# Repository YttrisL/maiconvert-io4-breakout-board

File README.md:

# maiconvert-io4-breakout-board

This breakout board is designed to be a helper for maimai FiNALE cabinet conversion to DX, to help people configure an IO4 home setup with a custom controller, or to serve as a testing setup for an IO4.

It can easily be installed between an IO4 and the cabinet harness thanks to its passthrough connector, supporting both FiNALE and genuine DX CN3 harnesses. If you do not have a harness to use, the board fans every I/O out to labeled JST-XH connectors and adds on-board test switches and RGB indicator LEDs.

<p align="center">

</p>
<p align="center"><sub>Schematic - PCB 3D render (front) - PCB 3D render (back) - click any image for the full-size version</sub></p>

<p align="center">

</p>
<p align="center"><sub>Fabricated and assembled board, wired to an IO4 and a generic PSU - top view - IO4 side - breakout board side</sub></p>

## Installation

The board requires 3 connections :

* You need to plug the CN3 and CN9 connectors from the IO4. The actual connector on IO4 is a JST-RA 2x30 pins, but you can use any connector with a pitch of 2.54mm. An IDC ribbon cable with two female connectors works great for that, you'll need a 2x30 and a 2x10.
* You also need to provide a clean 12V to the terminal block. If you're using the board in a cab, use the 12V PSU dedicated to LED lighting. Do not steal the 12V from the IO4.

There is basic protection at the entrance on the 12V rail on the board to prevent reverse polarity, but you are still responsible for providing clean current. The input is sized for 15A, though it should absolutely never reach that amount of current. There is a fuse right next to the connector. In case of issue, check that first.

## Use-cases

The board is intended for three parallel use-cases, designed with as little complexity and onboard logic as possible to ensure a minimal-to-null impact on gameplay. As such, you can use this board as a permanent addition to any cab without trade-off.

### Helper for maimai FiNALE cabinet conversion to DX

The main use-case. Install this board next to your IO4 in your FiNALE cab, connect CN3 and CN9 from the IO4, and plug in the cabinet's harness on the J3 connector.

There is a minor difference between the DX and FiNALE harness. On FiNALE's, the "Coin Locker" pin is at the position 51. On DX's, it is at the position 53, and 51 has been assigned to a billboard LED signal instead. To handle this difference, there are three pins right under the passthrough connector.

- **If your harness is a genuine DX (or an already modified FiNALE one)** :
  - Place a jumper over the two pins on the right
- **If your harness is an unmodified FiNALE** :
  - Place a jumper over the two pins on the left

The connection to the gameplay buttons is handled by the harness. However, since these do not exist on a FiNALE cab you will need to expose and connect the 1P and 2P SELECT BUTTONS to the appropriate JST-XH connectors.

The LED signals that DX now sends through the IO4 are exposed on the upper part of the board. You need to provide your own 12V power source for these to work. I advise using the cab's 12V LED PSU for this. Once properly powered, the test LEDs will light up with the signal sent by the game. You can now plug in your actual LEDs in the appropriate connectors. J23 and J24 for the billboard LED are designed to be compatible with the existing cables in a FiNALE cab covering the upper LEDs and the woofer LEDs. You will likely need a cable extension but you can plug those in directly on the board.

When the board has a CN3 harness plugged in on the passthrough J3 connector, only the `Test`, `Coin`, `Service`, and `1-2P Select` onboard tactile switches will work. The gameplay buttons' onboard tactile switches are disabled in this configuration.

Thanks to this, the board can be installed in the cab as a permanent addition with zero impact on performance.

### IO4 breakout board for home setup

If for your own reasons you want to run an actual IO4 in your home setup with your personal custom game controller, you can use this board to fan out the connectors from the IO4. Just connect the CN3 from the IO4 and plug in your buttons on the appropriate JST-XH connectors.

*Note :* the game expects buttons to be present. If you try running the board without plugging in the buttons, you will notice that the gameplay inputs are considered as continuously "pressed". See the "Test setup" case for ways to go around that, but it is not advised to use this board's tactile switches alone for actual gameplay.

If you want to install your own LEDs driven by the IO4, you can also do that. You need to plug in the CN9 connector with an IDC 2x10 female-female cable. You will also need to supply the 12V line with your own Mean Well PSU. Test LEDs should now light up as the game drives them and you can use the connectors to plug in your own LED strips. **Warning**: Do not put too much stress on the board, the copper is sized appropriately (excessively even) for the amount of current an actual cabinet's LED would draw, but if you put more load on the board then results may be unpredictable.

**Important note :** The game will not detect the IO4 if EXV is not bridged with 5V. In a normal cabinet, this is done by the harness. Here, **you need to install a jumper on the two dedicated floating pins situated next to the top right of the passthrough connector** normally dedicated to the harness.

In this configuration, both tactile buttons and gameplay buttons will work at the same time.

### A testing setup for an IO4

You may want to use the board to quickly test an IO4 you just received or you suspect faulty. Plug the CN3 and CN9 from the IO4, and plug your own 12V supply.

The LED section should light up as soon as the game starts driving them, you can use the onboard tactile switches to trigger the signals. Using it as-is though, you'll notice that the gameplay buttons' tactile switches do not actually work.

Because of the way the IO4 handles the gameplay buttons, it is normally not possible to test those signals if the actual button is not properly connected. This is because the IO4 natively puts that signal at HIGH, and the button assembly itself pulls it to LOW once it's connected. The IO considers that HIGH is "pressed", and LOW is "not pressed". Because of that behavior, unconnected buttons remain at HIGH and are always considered pressed.

To go around that, **for testing purposes you can put a jumper between pin 2 and 3 of the JST-XH connector**. That will bridge the signal in a forced LOW state that you can then activate using the onboard tactile button.

### Other uses

You might find other uses for this board that I hadn't thought about, though be aware that anything beyond the previous scope is not intended and the board behavior is not guaranteed.

## Fabrication

The PCB is designed to be fabricated bare at JLCPCB. See gerbers in `production/`.  
Components have to be hand-soldered. See the BOM in the `bom/` folder.

You can technically make JLCPCB assemble the board for you, but there are a lot of THT connectors on the board, and JLCPCB charges extra for each one of them. The extra price is most likely not worth the time, but you decide.

### To fab the PCB

On [jlcpcb.com](https://jlcpcb.com/) :

- Click "*Add gerber file*" and upload `production/maiconv-io4-breakout-board-gerbers.zip` as-is.
  - The auto-detected options already match this board (2 layers, 1.6 mm, 1 oz copper), just choose a solder mask color.
- Leave *PCB Assembly* off (all THT).
- Check the Gerber preview.
- Order.

### To order the parts

On [digikey.com](https://www.digikey.com/) :

- Go to *myLists* → *Create a New List* → *Upload a File* and upload `bom/digikey_upload.csv`.
- Map the columns to *Quantity* / *DigiKey Part Number* / *Customer Reference* (the header already uses those names).
- Review any out-of-stock lines, then add the list to your cart.
- Order.

## License

This board is distributed under the `CERN Open Hardware Licence Version 2 - Strongly Reciprocal` license. You are encouraged to share this page as much as you like and improve on the original design.

Please note that while the license doesn't strictly forbid it, I ask you to be a decent human being and to not make a business out of selling this board to anyone. This is free and should remain so. That being said, feel free to resell extra copies you may have gotten with your fabrication (they usually make them by stack of 5) to other people, as long as you do not charge an extortionate extra for them.

## Disclaimer

While I took great caution to make sure every component was properly sized, I am not a certified electronics engineer. This board is distributed freely without any guarantees, and you use it at your own risk. That being said, every component has been selected way above the actual minimal requirement of the circuit, so there shouldn't be any major issue.

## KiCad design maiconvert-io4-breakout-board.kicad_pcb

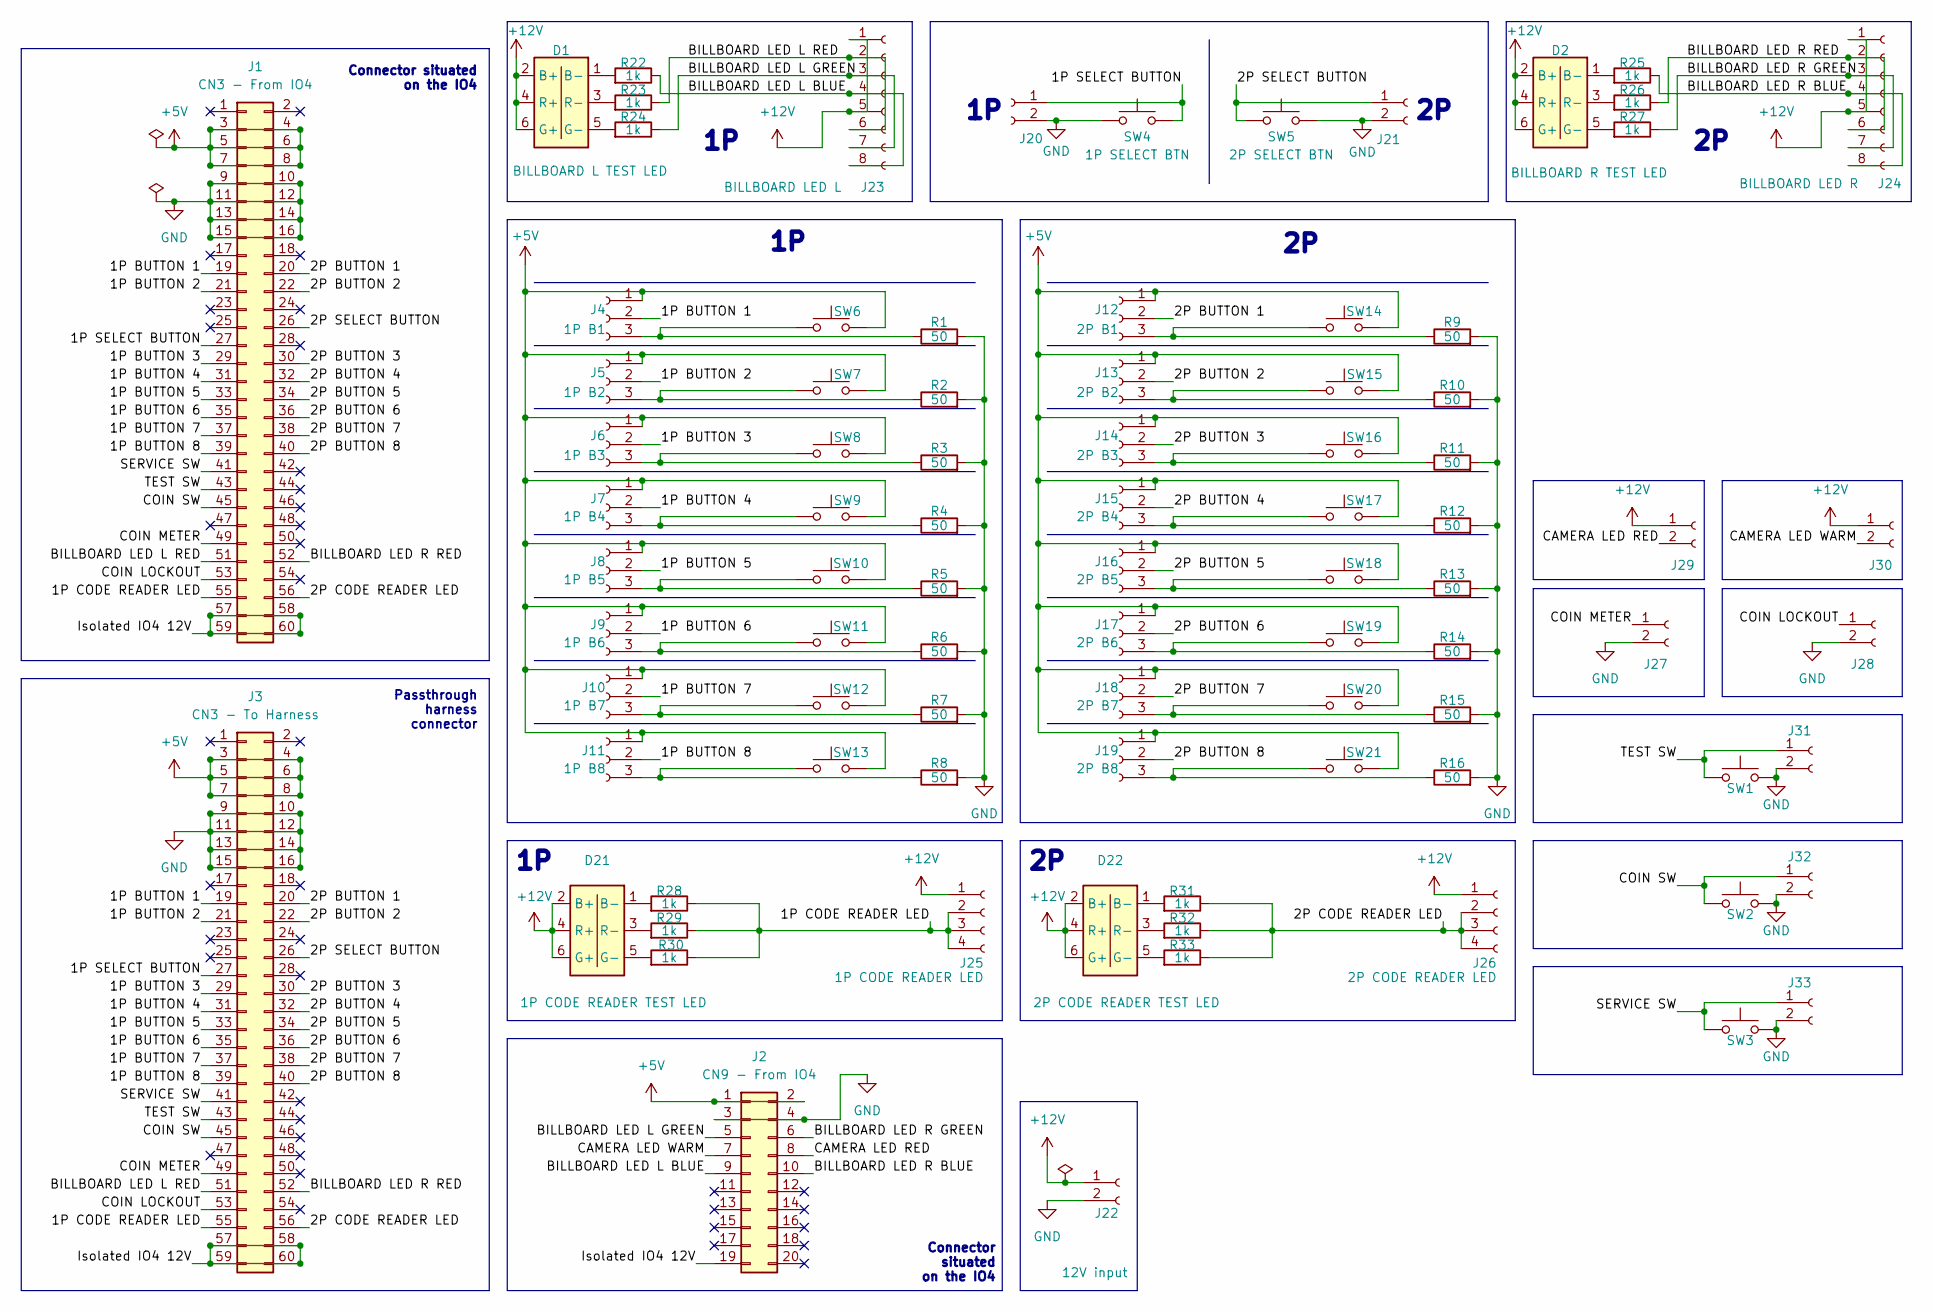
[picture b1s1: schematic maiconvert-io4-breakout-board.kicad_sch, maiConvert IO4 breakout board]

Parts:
D1: BILLBOARD L TEST LED; LED_RGB_Wurth_WL-SFTW_150352M173300; Digi-Key 732-11999-1-ND
D2: BILLBOARD R TEST LED; LED_RGB_Wurth_WL-SFTW_150352M173300; Digi-Key 732-11999-1-ND
D21: 1P CODE READER TEST LED; LED_RGB_Wurth_WL-SFTW_150352M173300; Digi-Key 732-11999-1-ND
D22: 2P CODE READER TEST LED; LED_RGB_Wurth_WL-SFTW_150352M173300; Digi-Key 732-11999-1-ND
J1: CN3 - From IO4; IDC-Header_2x30_P2.54mm_Vertical; Digi-Key 2057-BHR-60-VUA-ND
J2: CN9 - From IO4; IDC-Header_2x10_P2.54mm_Vertical; Digi-Key 2057-BHR-20-VUA-ND
J3: CN3 - To Harness; IDC-Header_2x30_P2.54mm_Vertical; Digi-Key 2057-BHR-60-VUA-ND
J4: 1P B1; JST_XH_B3B-XH-A_1x03_P2.50mm_Vertical; Digi-Key 455-2248-ND
J5: 1P B2; JST_XH_B3B-XH-A_1x03_P2.50mm_Vertical; Digi-Key 455-2248-ND
J6: 1P B3; JST_XH_B3B-XH-A_1x03_P2.50mm_Vertical; Digi-Key 455-2248-ND
J7: 1P B4; JST_XH_B3B-XH-A_1x03_P2.50mm_Vertical; Digi-Key 455-2248-ND
J8: 1P B5; JST_XH_B3B-XH-A_1x03_P2.50mm_Vertical; Digi-Key 455-2248-ND
J9: 1P B6; JST_XH_B3B-XH-A_1x03_P2.50mm_Vertical; Digi-Key 455-2248-ND
J10: 1P B7; JST_XH_B3B-XH-A_1x03_P2.50mm_Vertical; Digi-Key 455-2248-ND
J11: 1P B8; JST_XH_B3B-XH-A_1x03_P2.50mm_Vertical; Digi-Key 455-2248-ND
J12: 2P B1; JST_XH_B3B-XH-A_1x03_P2.50mm_Vertical; Digi-Key 455-2248-ND
J13: 2P B2; JST_XH_B3B-XH-A_1x03_P2.50mm_Vertical; Digi-Key 455-2248-ND
J14: 2P B3; JST_XH_B3B-XH-A_1x03_P2.50mm_Vertical; Digi-Key 455-2248-ND
J15: 2P B4; JST_XH_B3B-XH-A_1x03_P2.50mm_Vertical; Digi-Key 455-2248-ND
J16: 2P B5; JST_XH_B3B-XH-A_1x03_P2.50mm_Vertical; Digi-Key 455-2248-ND
J17: 2P B6; JST_XH_B3B-XH-A_1x03_P2.50mm_Vertical; Digi-Key 455-2248-ND
J18: 2P B7; JST_XH_B3B-XH-A_1x03_P2.50mm_Vertical; Digi-Key 455-2248-ND
J19: 2P B8; JST_XH_B3B-XH-A_1x03_P2.50mm_Vertical; Digi-Key 455-2248-ND
J20: 1P SELECT BUTTON; JST_XH_B2B-XH-A_1x02_P2.50mm_Vertical; Digi-Key 455-2247-ND
J21: 2P SELECT BUTTON; JST_XH_B2B-XH-A_1x02_P2.50mm_Vertical; Digi-Key 455-2247-ND
J22: 12V input; TerminalBlock_Phoenix_MKDS-1,5-2-5.08_1x02_P5.08mm_Horizont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; Digi-Key 277-1667-ND
J23: BILLBOARD LED L; JST_XH_B8B-XH-A_1x08_P2.50mm_Vertical; Digi-Key 455-B8B-XH-A-ND
J24: BILLBOARD LED R; JST_XH_B8B-XH-A_1x08_P2.50mm_Vertical; Digi-Key 455-B8B-XH-A-ND
J25: 1P CODE READER LED; JST_XH_B4B-XH-A_1x04_P2.50mm_Vertical; Digi-Key 455-2249-ND
J26: 2P CODE READER LED; JST_XH_B4B-XH-A_1x04_P2.50mm_Vertical; Digi-Key 455-2249-ND
J27: COIN METER; JST_XH_B2B-XH-A_1x02_P2.50mm_Vertical; Digi-Key 455-2247-ND
J28: COIN LOCKOUT; JST_XH_B2B-XH-A_1x02_P2.50mm_Vertical; Digi-Key 455-2247-ND
J29: CAMERA LED RED; JST_XH_B2B-XH-A_1x02_P2.50mm_Vertical; Digi-Key 455-2247-ND
J30: CAMERA LED WARM; JST_XH_B2B-XH-A_1x02_P2.50mm_Vertical; Digi-Key 455-2247-ND
J31: TEST BUTTON; JST_XH_B2B-XH-A_1x02_P2.50mm_Vertical; Digi-Key 455-2247-ND
J32: COIN BUTTON; JST_XH_B2B-XH-A_1x02_P2.50mm_Vertical; Digi-Key 455-2247-ND
J33: SERVICE BUTTON; JST_XH_B2B-XH-A_1x02_P2.50mm_Vertical; Digi-Key 455-2247-ND
R1, R2, R3, R4, R5, R6, R7, R8, R9, R10, R11, R12, R13, R14, R15, R16: 50; R_2512_6332Metric_Pad1.40x3.35mm_HandSolder; Digi-Key 118-CR2512-JW-510ELFCT-ND
R22, R23, R24, R25, R26, R27, R28, R29, R30, R31, R32, R33: 1k; R_1206_3216Metric_Pad1.30x1.75mm_HandSolder; Digi-Key 311-1.00KFRCT-ND
SW1: TEST; SW_PUSH_6mm; Digi-Key 2223-TS02-66-60-BK-100-LCR-D-ND
SW2: COIN; SW_PUSH_6mm; Digi-Key 2223-TS02-66-60-BK-100-LCR-D-ND
SW3: SERVICE; SW_PUSH_6mm; Digi-Key 2223-TS02-66-60-BK-100-LCR-D-ND
SW4: 1P SELECT BTN; SW_PUSH_6mm; Digi-Key 2223-TS02-66-60-BK-100-LCR-D-ND
SW5: 2P SELECT BTN; SW_PUSH_6mm; Digi-Key 2223-TS02-66-60-BK-100-LCR-D-ND
SW6: 1P B1 BTN; SW_PUSH_6mm; Digi-Key 2223-TS02-66-60-BK-100-LCR-D-ND
SW7: 1P B2 BTN; SW_PUSH_6mm; Digi-Key 2223-TS02-66-60-BK-100-LCR-D-ND
SW8: 1P B3 BTN; SW_PUSH_6mm; Digi-Key 2223-TS02-66-60-BK-100-LCR-D-ND
SW9: 1P B4 BTN; SW_PUSH_6mm; Digi-Key 2223-TS02-66-60-BK-100-LCR-D-ND
SW10: 1P B5 BTN; SW_PUSH_6mm; Digi-Key 2223-TS02-66-60-BK-100-LCR-D-ND
SW11: 1P B6 BTN; SW_PUSH_6mm; Digi-Key 2223-TS02-66-60-BK-100-LCR-D-ND
SW12: 1P B7 BTN; SW_PUSH_6mm; Digi-Key 2223-TS02-66-60-BK-100-LCR-D-ND
SW13: 1P B8 BTN; SW_PUSH_6mm; Digi-Key 2223-TS02-66-60-BK-100-LCR-D-ND
SW14: 2P B1 BTN; SW_PUSH_6mm; Digi-Key 2223-TS02-66-60-BK-100-LCR-D-ND
SW15: 2P B2 BTN; SW_PUSH_6mm; Digi-Key 2223-TS02-66-60-BK-100-LCR-D-ND
SW16: 2P B3 BTN; SW_PUSH_6mm; Digi-Key 2223-TS02-66-60-BK-100-LCR-D-ND
SW17: 2P B4 BTN; SW_PUSH_6mm; Digi-Key 2223-TS02-66-60-BK-100-LCR-D-ND
SW18: 2P B5 BTN; SW_PUSH_6mm; Digi-Key 2223-TS02-66-60-BK-100-LCR-D-ND
SW19: 2P B6 BTN; SW_PUSH_6mm; Digi-Key 2223-TS02-66-60-BK-100-LCR-D-ND
SW20: 2P B7 BTN; SW_PUSH_6mm; Digi-Key 2223-TS02-66-60-BK-100-LCR-D-ND
SW21: 2P B8 BTN; SW_PUSH_6mm; Digi-Key 2223-TS02-66-60-BK-100-LCR-D-ND

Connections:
+5V: J1.3, J1.4, J1.5, J1.6, J1.7, J1.8, J2.1, J2.2, J3.3, J3.4, J3.5, J3.6, J3.7, J3.8, J4.1, J5.1, J6.1, J7.1, J8.1, J9.1, J10.1, J11.1, J12.1, J13.1, J14.1, J15.1, J16.1, J17.1, J18.1, J19.1, SW6.2, SW7.2, SW8.2, SW9.2, SW10.2, SW11.2, SW12.2, SW13.2, SW14.2, SW15.2, SW16.2, SW17.2, SW18.2, SW19.2, SW20.2, SW21.2; also elsewhere on the board
/1P BUTTON 1: J1.19, J3.19, J4.2
/1P BUTTON 2: J1.21, J3.21, J5.2
/1P BUTTON 3: J1.29, J3.29, J6.2
/1P BUTTON 4: J1.31, J3.31, J7.2
/1P BUTTON 5: J1.33, J3.33, J8.2
/1P BUTTON 6: J1.35, J3.35, J9.2
/1P BUTTON 7: J1.37, J3.37, J10.2
/1P BUTTON 8: J1.39, J3.39, J11.2
/1P CODE READER LED: J1.55, J3.55, J25.2, J25.3, J25.4, R28.1, R29.1, R30.1
/1P SELECT BUTTON: J1.27, J3.27, J20.1, SW4.1
/2P BUTTON 1: J1.20, J3.20, J12.2
/2P BUTTON 2: J1.22, J3.22, J13.2
/2P BUTTON 3: J1.30, J3.30, J14.2
/2P BUTTON 4: J1.32, J3.32, J15.2
/2P BUTTON 5: J1.34, J3.34, J16.2
/2P BUTTON 6: J1.36, J3.36, J17.2
/2P BUTTON 7: J1.38, J3.38, J18.2
/2P BUTTON 8: J1.40, J3.40, J19.2
/2P CODE READER LED: J1.56, J3.56, J26.2, J26.3, J26.4, R31.1, R32.1, R33.1
/2P SELECT BUTTON: J1.26, J3.26, J21.1, SW5.1
/BILLBOARD LED L BLUE: J2.9, J23.4, J23.8, R22.1
/BILLBOARD LED L GREEN: J2.5, J23.3, J23.7, R24.1
/BILLBOARD LED R BLUE: J2.10, J24.4, J24.8, R25.1
/BILLBOARD LED R GREEN: J2.6, J24.3, J24.7, R27.1
/BILLBOARD LED R RED: J1.52, J3.52, J24.2, J24.6, R26.1
/CAMERA LED RED: J2.8, J29.2
/CAMERA LED WARM: J2.7, J30.2
/COIN LOCKOUT: J1.53, J3.53, J28.1; also elsewhere on the board
/COIN METER: J1.49, J3.49, J27.1
/COIN SW: J1.45, J3.45, J32.1, SW2.1
/EXV: J1.1, J1.2, J3.1, J3.2; also elsewhere on the board
/Isolated IO4 12V: J1.57, J1.58, J1.59, J1.60, J2.19, J3.57, J3.58, J3.59, J3.60
/NC 17: J1.17, J3.17
/NC 18: J1.18, J3.18
/NC 23: J1.23, J3.23
/NC 24: J1.24, J3.24
/NC 25: J1.25, J3.25
/NC 28: J1.28, J3.28
/NC 42: J1.42, J3.42
/NC 44: J1.44, J3.44
/NC 46: J1.46, J3.46
/NC 47: J1.47, J3.47
/NC 48: J1.48, J3.48
/NC 50: J1.50, J3.50
/NC 54: J1.54, J3.54
/SERVICE SW: J1.41, J3.41, J33.1, SW3.1
/TEST SW: J1.43, J3.43, J31.1, SW1.1
GND: J1.9, J1.10, J1.11, J1.12, J1.13, J1.14, J1.15, J1.16, J2.3, J2.4, J3.9, J3.10, J3.11, J3.12, J3.13, J3.14, J3.15, J3.16, J20.2, J21.2, J22.2, J27.2, J28.2, J31.2, J32.2, J33.2, R1.2, R2.2, R3.2, R4.2, R5.2, R6.2, R7.2, R8.2, R9.2, R10.2, R11.2, R12.2, R13.2, R14.2, R15.2, R16.2, SW1.2, SW2.2, SW3.2, SW4.2, SW5.2; also elsewhere on the board
unnamed: D1.1 (B-), R22.2
unnamed: D1.5 (G-), R24.2
unnamed: D1.3 (R-), R23.2
unnamed: D2.1 (B-), R25.2
unnamed: D2.5 (G-), R27.2
unnamed: D2.3 (R-), R26.2
unnamed 55: D21.1 (B-), R28.2; also elsewhere on the board
unnamed 56: D21.5 (G-), R30.2; also elsewhere on the board
unnamed 57: D21.3 (R-), R29.2; also elsewhere on the board
unnamed 58: D22.1 (B-), R31.2; also elsewhere on the board
unnamed 59: D22.5 (G-), R33.2; also elsewhere on the board
unnamed 60: D22.3 (R-), R32.2; also elsewhere on the board
unnamed: J4.3, R1.1, SW6.1
unnamed: J5.3, R2.1, SW7.1
unnamed: J6.3, R3.1, SW8.1
unnamed: J7.3, R4.1, SW9.1
unnamed: J8.3, R5.1, SW10.1
unnamed: J9.3, R6.1, SW11.1
unnamed: J10.3, R7.1, SW12.1
unnamed: J11.3, R8.1, SW13.1
unnamed: J12.3, R9.1, SW14.1
unnamed: J13.3, R10.1, SW15.1
unnamed: J14.3, R11.1, SW16.1
unnamed: J15.3, R12.1, SW17.1
unnamed: J16.3, R13.1, SW18.1
unnamed: J17.3, R14.1, SW19.1
unnamed: J18.3, R15.1, SW20.1
unnamed: J19.3, R16.1, SW21.1

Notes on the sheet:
Connector situated on the IO4
Connector situated on the IO4
Passthrough harness connector

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
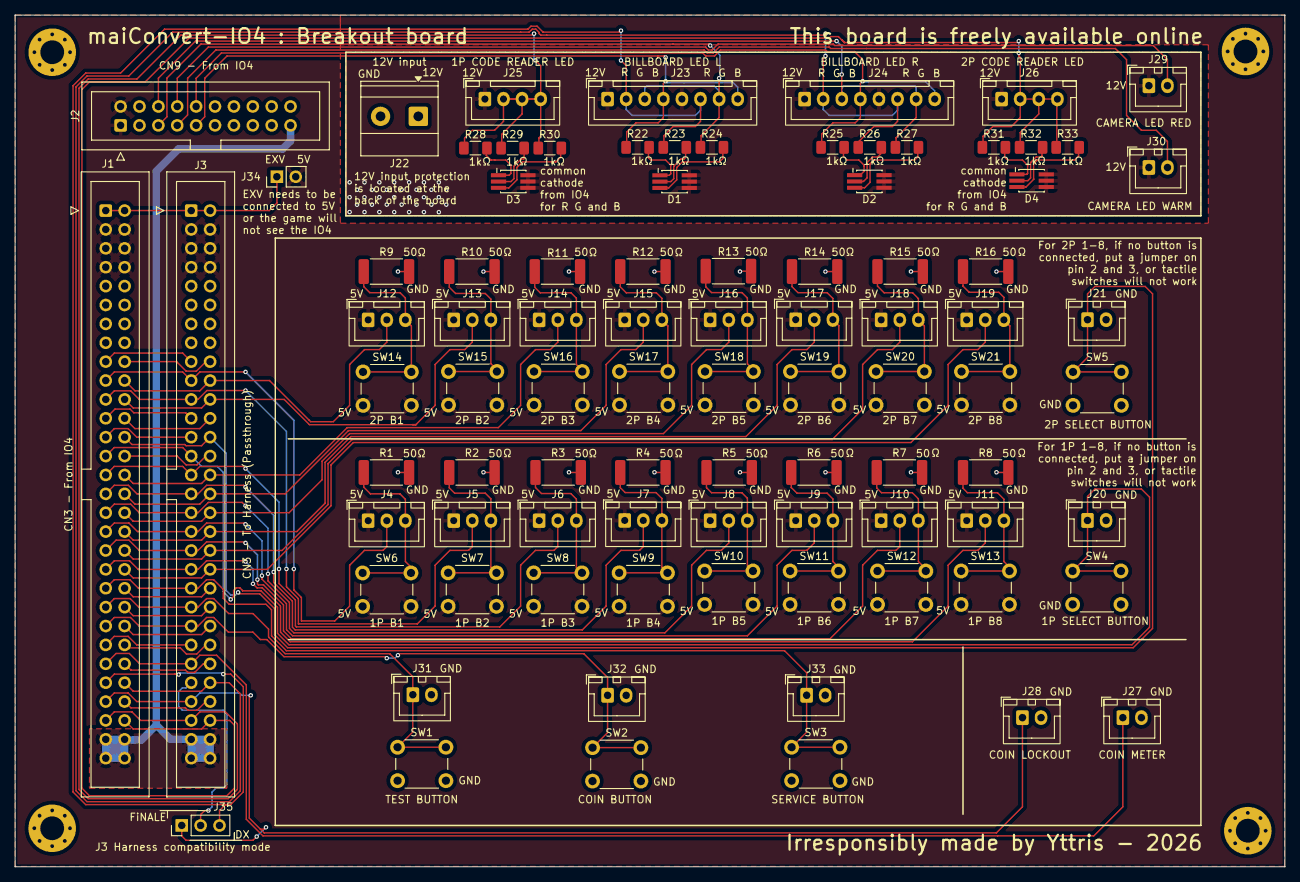
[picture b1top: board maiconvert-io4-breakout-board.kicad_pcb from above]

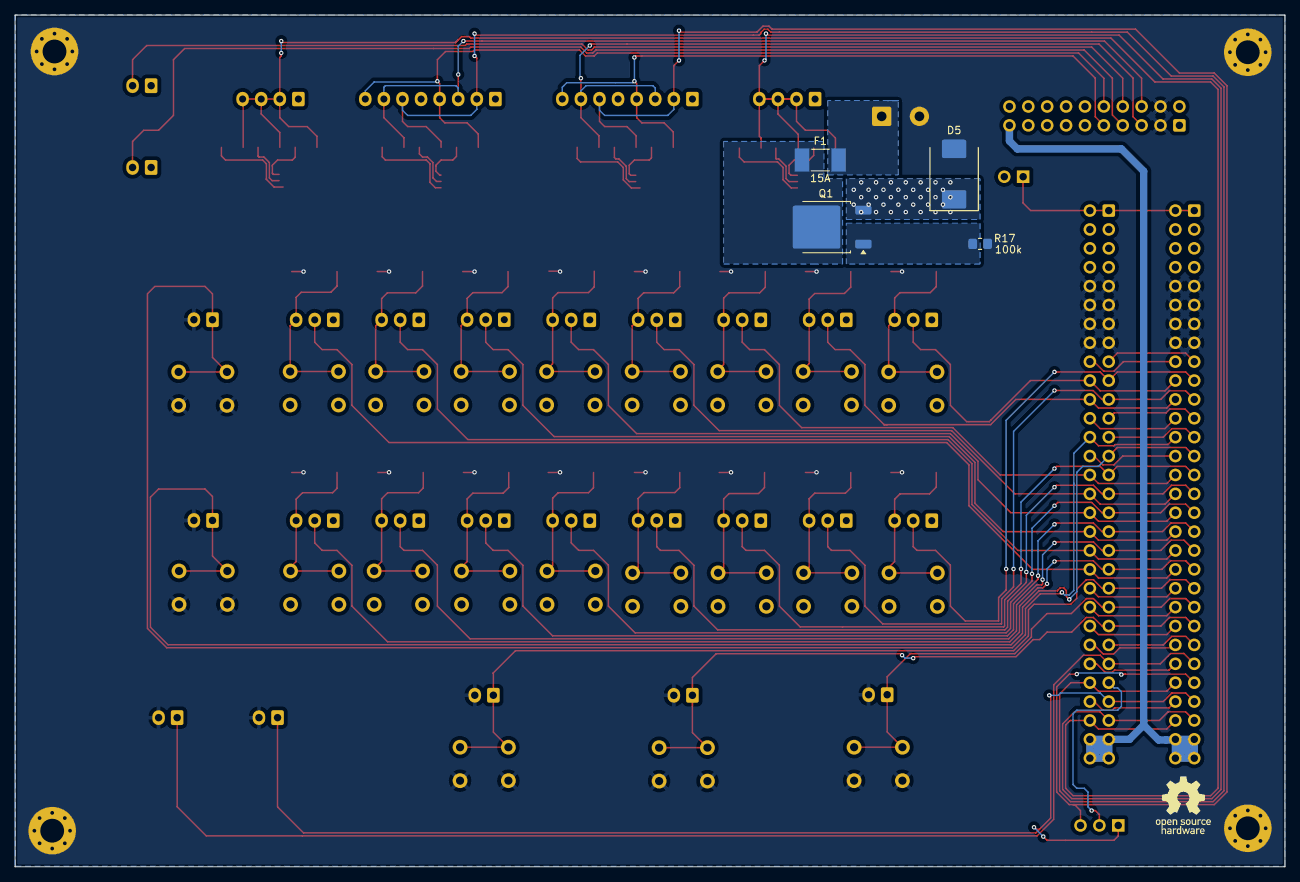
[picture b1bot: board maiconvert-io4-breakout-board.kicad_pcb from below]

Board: 2 copper layers, 170.8 x 114.6 mm, 92 parts (4 on the bottom side), 83 nets.

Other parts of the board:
D3: 1P CODE READER TEST LED; LED_RGB_Wurth_WL-SFTW_150352M173300
D4: 2P CODE READER TEST LED; LED_RGB_Wurth_WL-SFTW_150352M173300
D5: SMCJ15A; D_SMC
F1: 15A; Fuse_Littelfuse-NANO2-451_453
J34: EXV-5V Jumper; PinHeader_1x02_P2.54mm_Vertical
J35: Pin 51 Jumper; PinHeader_1x03_P2.54mm_Vertical
Q1: DMP3010LK3-13; TO-252-2
R17: 100k; R_0805_2012Metric_Pad1.20x1.40mm_HandSolder

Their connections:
+5V: J34.2; also elsewhere on the board
/COIN LOCKOUT: J35.1; also elsewhere on the board
/EXV: J34.1; also elsewhere on the board
GND: D5.2 (A2), R17.1; also elsewhere on the board
unnamed 55: D3.1 (B-); also elsewhere on the board
unnamed 56: D3.5 (G-); also elsewhere on the board
unnamed 57: D3.3 (R-); also elsewhere on the board
unnamed 58: D4.1 (B-); also elsewhere on the board
unnamed 59: D4.5 (G-); also elsewhere on the board
unnamed 60: D4.3 (R-); also elsewhere on the board
unnamed: F1.2, Q1.2 (D)
unnamed: Q1.1 (G), R17.2

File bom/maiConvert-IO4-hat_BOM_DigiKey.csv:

Item,Reference,Qty,Circuit,Description,Mfr,Mfr Part Number,DigiKey Part Number,Unit price USD approx,Footprint action,Notes
1,"R22,R23,R24,R25,R26,R27,R28,R29,R30,R31,R32,R33",12,-,"Resistance axiale 1 kOhm 1% 1/4W traversante",YAGEO,MFR-25FBF52-1K,1.00KXBK-ND,0.10,"Empreinte axiale (choisir l'entraxe, ex. 10,16 mm)","Resistances serie R/G/B des LED RGB. ~0,02 $ en bande de 10+. 5% carbone encore moins cher: CFR-25JB-52-1K (1.0KQBK-ND)."
2,"D1,D2,D21,D22",4,-,"LED RGB 6-PLCC / 5050 SMD, canaux independants",Wurth Elektronik,150352M173300,732-11999-1-ND,0.52,"REDESSINER empreinte + relier les 3 anodes ensemble (anode commune)","Seul composant SMD restant (4 pieces, se soude bien au fer). Carte = anode commune ; le schema pilote les cathodes R/G/B via R22-R33. Option 100% THT : Kingbright WP154A4SEJ3VBDZGW/CA (5 mm anode commune, 754-2029-ND, ~2,20 $)."
3,"SW1,SW2,SW3,SW4,SW5",5,SPST-NO,"Poussoir tactile 6 mm THT, NORMALEMENT OUVERT, momentane",Omron,B3F-1000,SW400-ND,0.40,"6 mm THT (garder)","NO. SW1 TEST / SW2 COIN / SW3 SERVICE / SW4 1P SELECT / SW5 2P SELECT. En parallele de J31/J32/J33/J20/J21. Budget: Same Sky TS02-66-70-BK-160-LCR (~0.10)."
4,"SW6,SW7,SW8,SW9,SW10,SW11,SW12,SW13,SW14,SW15,SW16,SW17,SW18,SW19,SW20,SW21",16,SPST-NC,"Bouton tactile SPST-NC (normalement ferme, appui = ouverture), momentane, CMS",Same Sky (ex-CUI),TS10-63-26-BE-250-SMT-TR,2223-TS10-63-26-BE-250-SMT-TRCT-ND,0.65,"Empreinte CMS 2 pattes, corps 6,0 x 3,8 mm (datasheet TS10)","*** NC - ne pas confondre avec SW1-5 (NO). *** En serie dans le retour GND de chaque bouton joueur ; un poussoir NO ici = boutons joueurs morts. Vrai tact-switch NC : appui = coupe le circuit. ~0,46 $ par 100. Seul bemol : CMS (2 languettes, se soude bien au fer). ~10 $ les 16. Force 250 gf, 0,05 A / 12 V (large pour du courant logique). Alternative THT : micro-rupteur SPDT COM+NC (CIT SM3 ~1,3 $)."
5,"J4,J5,J6,J7,J8,J9,J10,J11,J12,J13,J14,J15,J16,J17,J18,J19",16,-,"Embase JST XH male 1x03, pas 2,50 mm, verticale, THT",JST,B3B-XH-A(LF)(SN),455-2248-ND,0.13,"Garder","Boutons 1P/2P B1..B8."
6,"J20,J21,J27,J28,J29,J30,J31,J32,J33",9,-,"Embase JST XH male 1x02, pas 2,50 mm, verticale, THT",JST,B2B-XH-A(LF)(SN),455-2247-ND,0.11,"Garder","1P/2P SELECT, COIN METER, COIN LOCKOUT, CAMERA LED x2, TEST/COIN/SERVICE BUTTON."
7,"J25,J26",2,-,"Embase JST XH male 1x04, pas 2,50 mm, verticale, THT",JST,B4B-XH-A(LF)(SN),455-2249-ND,0.15,"Garder","1P / 2P CODE READER LED."
8,"J23,J24",2,-,"Embase JST XH male 1x08, pas 2,50 mm, verticale, THT",JST,B8B-XH-A(LF)(SN),455-B8B-XH-A-ND,0.28,"Garder","BILLBOARD LED L / R. Ancien n DigiKey 455-2251-ND retire."
9,"J1,J3",2,-,"Box header IDC a detrompeur 2x30 (60 pos), pas 2,54 mm, vertical, THT",Adam Tech,BHR-60-VUA,2057-BHR-60-VUA-ND,1.80,"Garder, ou header nu 2x30 (~0,40) si pas de nappe a detrompeur","CN3 From IO4 / CN3 To Harness."
10,"J2",1,-,"Box header IDC a detrompeur 2x10 (20 pos), pas 2,54 mm, vertical, THT",Adam Tech,BHR-20-VUA,2057-BHR-20-VUA-ND,0.70,"Garder, ou header nu 2x10 (~0,15)","CN9 From IO4."
11,"J22",1,-,"Bornier a vis 2 poles, pas 5,08 mm, THT",Phoenix Contact,1935161,277-1667-ND,1.40,"Pas 5,08 mm : tout bornier 5,08 mm 2P convient","Entree 12 V. Equivalent eco: Same Sky TB007-508-02BE (~0.40)."
